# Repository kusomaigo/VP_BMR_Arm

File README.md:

# VP BMR Speaker Arm

---

Simple speaker arm incorporating a Tectonic BMR (TEBM35C02-6B, same model as those in the Valve Index) for use with a Vive Pro headset headstrap.

Uses the built-in DAC and speaker arm connections of the Vive Pro headset and headstrap.

The friction pad part should be printed in a soft material (or cut out of one) to use as a friction pad between the speaker arm and "clipper".

The speaker clip may need minor resizing in the slicer to result in a part that snaps correctly over the speaker arm.

## Required Additional Material (Assembly)

- 1x M4 Round Cap Hex Screw, 12mm
- 1x M4 Lock-Nut
- 1x M2.5 Screw, 6mm (x2, optional)
- 1x M2.5 Threaded Insert, 4mm (x2, optional)
- 2x M3 Screw, 8mm
- 2x M3 Threaded Insert, 5mm

## Required Components (per PCB)

- 4x 5mm Spring Loaded Contacts: ED10177-ND
- 1x 4.3k Resistor, 0603

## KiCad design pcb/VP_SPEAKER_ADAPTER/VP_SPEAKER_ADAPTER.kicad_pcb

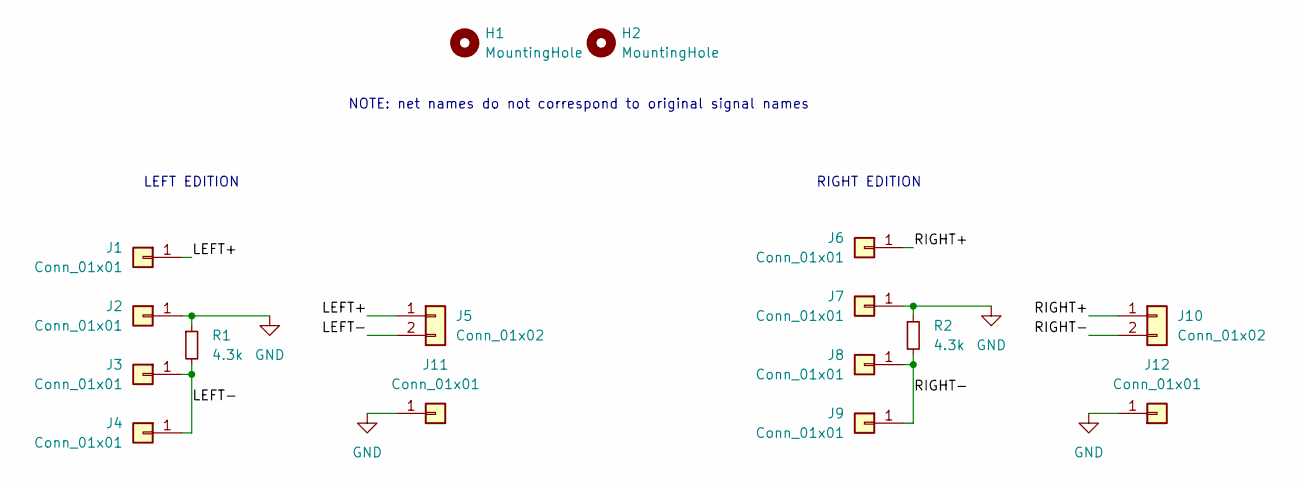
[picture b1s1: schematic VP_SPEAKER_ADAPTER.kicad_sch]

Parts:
H1, H2: MountingHole; MountingHole_2.7mm_M2.5
J1, J2, J3, J4, J6, J7, J8, J9: Conn_01x01; 0964-0-15-20-85-14-11-0
J5, J10: Conn_01x02; 2-contact-patch
J11, J12: Conn_01x01; 1-contact-patch
R1, R2: 4.3k

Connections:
/LEFT+: J1.1, J5.1
/LEFT-: J3.1, J4.1, J5.2, R1.2
/RIGHT+: J6.1, J10.1
/RIGHT-: J8.1, J9.1, J10.2, R2.2
GND: J2.1, J7.1, J11.1, J12.1, R1.1, R2.1

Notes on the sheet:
RIGHT EDITION
LEFT EDITION
NOTE: net names do not correspond to original signal names

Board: 2 copper layers, 28 parts (13 on the bottom side), 5 nets, no tracks yet.

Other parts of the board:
kibuzzard-625A70B4: G***; kibuzzard-625A70B4
kibuzzard-625A7081: G***; kibuzzard-625A7081
kibuzzard-625A7373, kibuzzard-625A7373#2, kibuzzard-625A7373#3, kibuzzard-625A7373#4: G***; kibuzzard-625A7373
kibuzzard-6296FBFD, kibuzzard-6296FBFD#2: G***; kibuzzard-6296FBFD
kibuzzard-6296FC15, kibuzzard-6296FC15#2: G***; kibuzzard-6296FC15
kibuzzard-6296FC21, kibuzzard-6296FC21#2: G***; kibuzzard-6296FC21

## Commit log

2022-06-01 init commit
2022-06-01 quick fix readme
2022-06-01 add speaker clip obj
2022-06-01 fancy old image
2022-06-01 think remembered everything for parts...
2022-06-01 image is smaller now
